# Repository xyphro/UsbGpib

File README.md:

# Table of contents

:newspaper: [Latest updates](Updates.md)
<br> :hammer: [Buy it or build it](#buy-it-or-build-it)
<br> :wave: [UsbGpib Introduction](#usbgpib-introduction)
<br> :house: [Housing / Enclosure](#housings)
<br> :computer: [Software](#software)
<br> &nbsp; &nbsp; :electric_plug: [Using the device](#using-the-device)
<br> &nbsp; &nbsp; :gear: [Setting and getting parameters](#setting-parameters)
<br> :heavy_check_mark: [Testing status](#testing-status)
<br> :notebook: [Tutorials](Tutorials/README.md) <- **New!**
<br> :heart: [Support the Project](#support-the-project)

# Summarized latest updates

For detailed visibility look under the Latest update link above!

[18th Apr 2026]: **Released Firmware V2.4: Added support for multiple GPIB devices**

[18th Apr 2026]: **Added some updated notes on GPIBee**

[07th Mar 2026]: **USbGpib V2 back in Stock on Elecrow**  

[07th Mar 2026]: **10 UsbGpib V3 == GPIBee prototypes ready for testing**

# Next version update USBGpib V3 

**UsbGpib V3 has a Name - Introducing GPIBee**

...and as you’ll see in the picture: The beauties are ready!

After months of development, redesigns, loosing hair on fixing SW bugs and teasing the new Ethernet + PoE capabilities, the next generation of UsbGpib finally has its official identity. From this point forward, UsbGpib V3 will be known as GPIBee - a compact, fast, and delightfully capable little worker that's ready to buzz around your lab equipment.

PoE is fully operational, VXI-11 supports multiple simultaneous connections, and USB High-Speed is performing flawlessly - on MY bench. Which does not mean (yet) on everybody elses bench. Testing is by multiple people is always very important!

I now have ten GPIBee prototypes fully assembled and sitting proudly on my desk. These units will soon head out to the first wave of beta testers who’ve been following the journey and are eager to put them through real‑world use.
I had hoped to start shipping next week, but with Embedded World taking up my entire schedule, distribution will begin shortly after I'm back. The excitement doesn't slow down - it just builds a little more.

Thank you all for the incredible support, feedback, and enthusiasm.

GPIBee is about to take its first flight, and you're part of the swarm that made it possible.
Stay tuned - beta testing starts soon, and the prototypes look fantastic.

## GPIBee update 18th April: 

The first prototypes have been shipped, and internal testing is already well advanced.  
Across all protocols, read performance shows a **3.5× to 5× speed increase**, and this is **without** any dedicated speed-optimization work applied yet.

## Communication Modes

### USB Interface

GPIBee supports three independent USB-based communication modes:

1. **Network mode**  
   GPIBee exposes a USB-based Ethernet interface. An IP address is assigned automatically, enabling true plug-and-play operation.  
   - Full **VXI-11** support  
   - Integrated **web server** providing configuration pages, a GPIB command console, and the complete manual matching the currently installed firmware  
   - Ideal for multi-device setups and remote control - it should be considered as the first Goto solution in terms of USB based modes.

2. **USBTMC mode**  
   Similar to **UsbGpib V2**, but extended with additional commands, including the ability to set the target **GPIB device address** — enabling communication with multiple GPIB instruments.

3. **++ protocol mode**  
   Exposes a **USB CDC UART** implementing the popular ++ protocol, compatible with existing controllers using that protocol — but at significantly higher speed.

The USB modes are **mutually exclusive**. The active mode can be selected via the **web interface** or through internal **SCPI commands**.

### Ethernet Interface

1. **VXI-11**  
   Provides multiple logical channels, allowing communication with several GPIB devices simultaneously without manually switching addresses between commands. 
   - Proper **lock handling** for multi-client access  
   - Full **SRQ** support  
   - Full **GPIB subaddressing** support

2. **++ protocol**  
   Optional **TCP/IP** service on port **1234**, offering the same `++` protocol implementation as in USB CDC UART mode.

Both Ethernet protocols can be **active at the same time**. The Ethernet interface also exposes the same **web interface** as USB network mode, enabling GPIB transfers, configuration changes, and access to the **firmware-synchronized manual**.

## GPIBee Beta Testing Status

The current beta focus remains on **functional correctness and stability**.  
**Speed optimization** will follow next.

For testers not having received an adapter yet: Additional prototype units will be shipped soon. Handling too many testers at once would otherwise become too **time-intensive**.

---

# Buy it or build it

* Tired of tinkering? Want to skip the hassle and get straight to using your GPIB setup?  
* You’d rather spend your time using your instruments instead of assembling hardware?

Skip the soldering iron and jump straight into your GPIB workflow!

You’ve got two solid options to get a ready‑to‑run UsbGpib adapter.

## &#x1f1fa;&#x1f1f8; - United States
* If you're in the US, you can now order the UsbGpibV2 directly from several sources, including my distribution partner Binho LLC. Enjoy fast domestic shipping with no long waits, no customs paperwork, and no surprises - just quick delivery and a smooth experience: 
<br> &#x1F449; <a href="https://binho.io/test-measurement/products/usbgpib-v2/" target="_blank">https://binho.io/test-measurement/products/usbgpib-v2/</a>
<br> &#x1F449; <a href="https://www.digikey.com/short/29nqq5cz" target="_blank"> https://www.digikey.com/short/29nqq5cz</a>
<br> &#x1F449; Amazon US also has it listed, but right now no stock, but worthwhile to check it out there too.

## &#x1F30E; - Worldwide
* I’ve teamed up with Elecrow to bring you ready-to-roll GPIB-USB converters – perfect for those who want results, not a weekend project.
* These adapters come fully assembled, programmed, housed, tested, and ready to go. No fuss. No build. Just plug it in and start working.
* The Adapters match 100% the V2 version described in this repository. 
* &#x1F449; <a href="https://www.elecrow.com/xyphrolabs-gpibusb.html" target="_blank">https://www.elecrow.com/xyphrolabs-gpibusb.html</a>

Let the data flow begin!

This doesn’t mean I’m going fully commercial - far from it.
Offering pre-built adapters is simply a convenience for those who’d rather skip the build and get straight to using their gear.

All sharing, support, and collaboration will remain fully open, just as before.
This is about choice, not change!

The full design files are located in this repository in case you want to build the devices yourself.

---

# UsbGpib Introduction
Versatile, cheap, portable and robust USB to GPIB converter (USBTMC class based).

You'll find many projects like this, but this one is special (ok, everybody will claim this) :-)

V1 Hardware: 

V2 Hardware: 

If you have a lot of test equipment at home, you might know the issues: Lots of devices only have GPIB as interface and the GPIB adapters and GPIB cables on the market are very expensive and some of them even have many issues, when run under Windows 10 (device driver does not work). Or they e.g. are not able to be operated with VISA, because they are UART based, need special command sequences, ...

The adapters are also typically very long, such that they extend the overall length of your test equipment by at least 10cm (~4 inches).

Apart of the 2 very big manufacturers, other GPIB adapters, e.g. with Ethernet or also USB interface are not recognized by normal VISA providers or PyVisa, making the measurement control implementation specific for your GPIB adapter.

I've got frustrated and tried to turn it into something positive. Here a video showing the final device in action - click to view:

Some goals of the project were:
- Work based on the standard USBTMC protocol. This allows the GPIB test equipment to look like a normal USB based measurement device and work flawless with e.g. NI VISA, Labview, Matlab or PyVisa.
- Have a small length - otherwise my equipment has the risk of falling from the shelf :-) Also the USB cable should connect 90 degree angled, to make it very short. With V2 HW, the length got further reduced to the size of a GPIB connector.
- It should be cheap but still versatile (you can build a single one of these for only 14 USD!)
- It should support ALL my test equipment, from many different GPIB implementation generations and different GPIB flavors
- The Firmware should be upgradeable over USB
- It should be rock-solid (!) I don't want to end up in a very long measurement being interrupted because of a software issue of my USB GPIB converter.
- It should support additional features like serial poll, remote enabling/disabling
- If there is no GPIB device connected to the USBGpib converter, or the GPIB device is powered down, there should be no USB device visible on the PC.

All those goals are met.

---

# Hardware

## Microcontroller choice

Although I typically would prefer nowadays an ARM Cortex M0/3/4/7 controller, there is an issue with it. Available devices support only max. 3.3V supply voltages, such that there would be a requirement for a level-shifter towards the GPIB Bus.
GPIB is based on 5V (not exactly true, but a first iteration).

This limited the microcontroller choice to e.g. AVR or PIC controllers. Because of very good availability I ended up in ATMEGA32U4 controllers.
Apart of the device supporting 5V I/O voltages, it also does not require a regulator to be part of the application - it has an internal 3.3V regulator. This minimizes the full application schematic and BOM.

Apart from that, there is an excellent USB stack available [http://www.fourwalledcubicle.com/LUFA.php](http://www.fourwalledcubicle.com/LUFA.php).

The GPIB side of the schematic can be directly connected to the ATMega32U4 IO pins. The IO pins from the microcontroller side are only set to 2 different states: Tri-state (input) or output LOW, to talk over GPIB.

## Component sourcing

All components are easy to source, so I only specify the potential critical ones:

- 16 MHz Crystal: Farnell 2853867 - MCSJK-7E-16.00-8-30-100-B-30 
- REV 1 GPIB connector: Farnell 2421095 - NORCOMP 112-024-113R001. For REV 2 use a straight 24P male solder type connector e.g. from AliExpress.
- USB connector for V1 HW: Farnell 2668483 - Amphenol ICC 61729-1011BLF
- USB connector for V2 HW: Best is to look on AliExpress for 57 series 24P connector as a starting point.

## PCB

The PCB can be ordered at nearly any PCB pool production service (e.g. 10 PCBs for 2 USD + shipping). The gerber files are included in the "HW/Gerber files" subdirectory.

## Mounting the PCB & Flashing the firmware

The PCB is available in 2 revisions.
- [REV 1](HW/REV1/README.md) is the most popularly used right now due to age. It has a USB Type-B connector and an L-shaped housing visible on a few photos of this page.
- [REV 2](HW/REV2/README.md) has some improvements like being smaller, better fit and USB Type-C connector.
- A REV 3 is upcoming. It will be a major redesign with more speed, Ethernet and power over Ethernet support, but the same DNA: Standard protocols being used and ensure compatibility and stability!

Choose whatever you prefer. The software images, but also the external behavior is the same.

---

# Housings

## REV 1

I created a sophisticated 3D printable housing for this adapter. The design was made with Fusion 360. The project file + the STL files are included in the "Housing" sub directory.

The PCB fits perfectly into it. Optionally it can be fixed with 2 mounting screws (the GPIB connector has 2 threads, use 2 times 4-40 UNC x 3/8) and the TOP cover snaps onto the housing base.

I printed this using an Ender 5 3D printer with black PLA, 0.15mm layer height, 1mm wall thickness, no support.
Take care, that you rotate the TOP part of the housing by 180 degrees, so that the flat side is located on the printer bed.
Printing works fine, several iterations of the design were made to ensure good printability.
I printed so far 15 housings, without a single fail.

More information on this REV 1 can be found here: [REV 1](HW/REV1/README.md).
Note, that also the programming/build instructions moved to this location.

## REV 2

The REV 2 housing is a lot smaller, but requires 2 screws.
The housing is quite important to be able to connect and disconnect the board without breaking anything. It is key for mechanical stability of the adapter.
When operating the device without housing, take very well care when plugging in and out the board in case the GPIB connector has a very tight fit.

Information on how to build it can be found in the HW/REV 2 folder: [REV 2](HW/REV2/README.md).
Note, that also the programming/build instructions moved to this location.

---

# Software

## Source code

The source code of the Boot loader (slightly modified LUFA MassStorage Boot loader) and the main USBGPIB converter are located in the "SW" subdirectory.
At the time of publication LUFA 170418 release was used, with GCC as compiler.

Note: The Software is compatible with any HW revision in this repository. For REV 1 and REV 2 hardware you don't need different SW images.

## Binaries

For those, that just want to create their own device, I've included the binary output in the "SW/binaries" subdirectory.

---

# Using the device

## USB enumeration

You might be surprised initially, that the device does not show up in your device manager (or lsusb), when you connect only the USB side. This is a feature, not a bug (really!).
Only, if a GPIB device is connected, you can see the device on your PC too.

The reason behind the feature is simple: Instead of having a standard GPIB wiring, where you have a single GPIB controller and lots of GPIB devices interconnected, USBGPIB supports only a direct connection of the USBGPIB device to your measurement device. If you have like me e.g. 14 Instruments you don't want all to show up in the device manager, if the measurement device itself is powered down - you won't anyway be able to communicate with a powered down device.

When USB and the GPIB side is connected, the device enumerates. The USBGPIB device reads out the ID of the instrument and constructs a unique USB Serial number out of it. It is thus easily possible to assiate multiple connected USBGPIB devices with the measurement instrument.

The VISA ressource name is constructed from this USB Serial number. You can identify easily e.g. in NiMax, which device is connected:

If you connect your USBGPIB device afterwards to another GPIB measurement device, it will disconnect and connect with a new serial number string, matching the other GPIB device *IDN? response again.

## GPIB settings on your measurement device

GPIBUSB does probe all GPIB primary addresses (and secondary address 0) for presence of a GPIB Talker/listener. It is thus not required to set a specific GPIB address - GPIBUSB will find it itself.

The only importance setting on the measurement device is, that the GPIB interface is enabled, which is typically the case.

## LED indicator

The LED indicates different states:

LED blinking: The USBGPIB converter is connected to a measurement instrument, it is powered off or its GPIB port is disabled. In this state, the device is also not connected to USB and will not show up in the device manager or lsusb.
LED on: The device is connected to a measurement device and GPIB communication possible. It is also accessible over USB
LED off: The device is not connected over USB, or the PC powered off :-)

## Controlling GPIB devices

As this converter implements the standard USBTMC Test and measurement class, you can control your instrument from ANY of the normal VISA tools. I tried so far R&S VISA and NI Visa, using Python and Matlab to talk to the devices.

# Testing status

This project is actively maintained since more than 6 years and I personally consider it as very stable. It is proven by multiple users to operate on MacOSX, Linux and Windows and measurement equipment from several decades.

In general I take bug reports very serious and want to "fix them all". In case you don't get an answer on-time on items you report in the issues section, please write me: Xyphro@gmail.com. 
I often miss seeing issue reports very quickly, as I don't get an email once they are filed.

## Sucessfully tested measurement equipment:

Below list is equipment I mainly myself tested. Many other users have other measurement equipment proven in use already.

- R&S FSEM30
- R&S SMIQ03
- R&S CMU200
- R&S SMW200A
- R&S FSW
- R&S FSV
- Keithley 199 multimeter
- HP 34401 DMM from different generations / with different FW versions
- HP 3325A synthesizer/frequency generator
- HP 3457A multimeter
- Agilent E4406A VSA transmitter tester
- Tektronix TDS7104 Digital Phosphor Oscilloscope
- HP 8596A spectrum analyzer
- Agilent E3648A dual power supply

## Scenarious

- It works under all popular operating systems like Windows 7 and 10, 11, Linux and MacOSX
- USB1.1, USB2.0 and USB3.x ports tested, with and without USB HUB in between.
- The connection stays responsive, when power cycling the PC, or hibernating/sleeping it
- Different connection cycles (GPIB side connected first, USB side connected first, swapping GPIB side equipment, ...)
- Extensive testing of timeout scenarious. E.g. making an illegal query and testing, if the USBTMC handles the timeouts properly. This was a very tricky part to get right.
- Tested special transfer modes. E.g. capturing screenshots from different equipment is usually something, which will drive other GPIB adapters to the limits, because binary data of unknown length needs to be transported successfully.

# Setting Parameters

The firmware version from 13th January 2024 onwards has the ability for human readable text base configuration of several parameters.
The previous methods are still supported, but won't be further documented. You can look them back in the history of this file.

The command parser is quite simple. For that reason follow the exact syntax as shown below. 
Don't add extra spaces or make other modifications or concatenate commands.

## Read termination method

While most GPIB interfaces use the hardware signal EOI to signal the end of a message, not all old equipment supports it. Some older instruments even don't have the EOI pin hardware wise wired and use \r or \n termination.

The USB-TMC standard allows to set the read termination. While in firmware versions before < 2.0 I did not enable that method, it is now finally supported with standard compliance.

I document here the older method (using pulse indicator request), but I add also the newer methods which are 100% UsbTmc compliant and portable across different equipments. You can choose which ones to use, but in some cases pulse indicator requests can be difficult to issue, for which reason it is likely better to use the standard compliant method.

### Set read termination to CR (\r):
(old method)
```
dev.control_in(0xa1, 0x40, 0, 0, 1); # USBTMC pulse indicator request (enables internal command processing)
dev.write('!term cr')
```
Above setting is volatile. To make this a permanent setting call the below mentioned "!term store" command.

(prefered method) Alternatively you can set the termination directly with visa means, e.g. using PyVisa:
```
dev.set_visa_attribute(visa.constants.VI_ATTR_TERMCHAR_EN, True)
dev.set_visa_attribute(visa.constants.VI_ATTR_TERMCHAR, ord('\r') )
```

### Set read termination to LF (\n):
(old method)
```
dev.control_in(0xa1, 0x40, 0, 0, 1); # USBTMC pulse indicator request (enables internal command processing)
dev.write('!term lf')
```
Above setting is volatile. To make this a permanent setting call the below mentioned "!term store" command.

(prefered method) Alternatively you can set the termination directly with visa means, e.g. using PyVisa:
```
dev.set_visa_attribute(visa.constants.VI_ATTR_TERMCHAR_EN, True)
dev.set_visa_attribute(visa.constants.VI_ATTR_TERMCHAR, ord('\n') )
```

### Set read termination to EOI only (default setting):
(old method) 
```
dev.control_in(0xa1, 0x40, 0, 0, 1); # USBTMC pulse indicator request (enables internal command processing)
dev.write('!term eoi')
```
Above setting is volatile. To make this a permanent setting call the below mentioned "!term store" command.

(prefered method) Alternatively you can set the termination directly with visa means, e.g. using PyVisa:
```
dev.set_visa_attribute(visa.constants.VI_ATTR_TERMCHAR_EN, False)
dev.set_visa_attribute(visa.constants.VI_ATTR_TERMCHAR, ord('\0') )
```

### Save readtermination setting in eeprom (make them non-volatile)
```
dev.control_in(0xa1, 0x40, 0, 0, 1); # USBTMC pulse indicator request (enables internal command processing)
dev.write('!term store')
```

Above relates to the "old non prefered method". In general it is a good idea to set the read termination volatile and use the above suggested methods highlighted with (prefered method).

### Query current termination setting from device
```
dev.control_in(0xa1, 0x40, 0, 0, 1); # USBTMC pulse indicator request (enables internal command processing)
print(dev.query('!term?'))
```
This returns a text string containing "lf", "cr" or "eoi"

## Multi-device support - Setting the GPIB device target address

Since Firmware version V2.4 USBGpib allows supporting multiple instruments.

While the USBTMC protocol allows only setting a single device to be addressed and composite USB devices are not well supported by all VISA implementations, I decided to add a command to set the address of the GPIB device which is addressed.

There is a minor limitation of this approach, which is that service request SRQ handling is only done properly to the currently selected GPIB device.
Another one is, that users shall never forget to set the GPIB address to the correct setting before issuing a command.

### Setting a primary address only

Substitute the text <Primary_address> with a number from 1 to 30 to set the primary address of the new GPIB device to talk to in following GPIB transactions

```
dev.control_in(0xa1, 0x40, 0, 0, 1);
dev.write('!addr <Primary_address>')
```

### Setting a primary + secondary address

Substitute the text <Primary_address> with a number from 1 to 30 to set the primary address and <Secondary_address> with a number from 0..6 or 96..102 of the new GPIB device to talk to in following GPIB transactions.
Note, that not the full subaddress range of 0..31 or 96..127 is supported as of now - this requires a bit more work. Most common device with subaddresses like R&S CMU200 only are well covered with that current range.

```
dev.control_in(0xa1, 0x40, 0, 0, 1);
dev.write('!addr <Primary_address> <Secondary_address>')
```
### Python wrapper example code for GPIB address setting

```
import pyvisa as visa
dev = 'USB0::0x03EB::0x2065::GPIB_22_14236333938351C00011::INSTR'
rm = visa.ResourceManager()
dev = rm.open_resource(dev, open_timeout=1000)

def set_gpib_addr(primary_address, secondary_address = None):
    dev.control_in(0xa1, 0x40, 0, 0, 1);
    if secondary_address is None:
        dev.write('!addr %d' % primary_address);
    else:
        dev.write('!addr %d %d' % (primary_address, secondary_address));
    
# Address CMU200, which is for me on primary address 1, secondary address 0
set_gpib_addr(1, 0)
print(dev.query('*IDN?'))

# address HP3457A on primary GPIB address 22
set_gpib_addr(22)
dev.write('END,ALWAYS')
print(dev.query('ID?'))
```

This code results in my current testsetup with CMU200 and HP3457A in this output:

```
Rohde&Schwarz,CMU 200-1100.0008.02,xxxxxx,V5.22

HP3457A
```

## AutoID setting

Default wise the GPIB adapter tries during power on of the instrument to query using *IDN? or ID? commands the instrument name automatically.
This is used to build the USB serial number, which finally gets part of the VISA ressource string.

Not all instruments support this *IDN / ID? query. For this reason this feature can be turned off.
The serial number will then be built based on the GPIB address of the instrument.

### Turn AutoID feature off
```
dev.control_in(0xa1, 0x40, 0, 0, 1); # USBTMC pulse indicator request (enables internal command processing)
dev.write('!autoid off')
```
This setting is stored in eeprom = non volatile memory, so will survive a power cycle

### Turn AutoID feature on
```
dev.control_in(0xa1, 0x40, 0, 0, 1); # USBTMC pulse indicator request (enables internal command processing)
dev.write('!autoid on')
```
This setting is stored in eeprom = non volatile memory, so will survive a power cycle

### turn auto ID on with delay

Some instruments need after turn on some seconds before GPIB is responsive.

With below 3 settings you can set a delay which is applied before the instrument ID is queried after power on.
Note that it will take then also more time, before the USB device is recognized by the PC.

Also this setting is non-volatile.

Delay 5 seconds:
```
dev.control_in(0xa1, 0x40, 0, 0, 1); # USBTMC pulse indicator request (enables internal command processing)
dev.write('!autoid slow')
```

Delay 15 seconds:
```
dev.control_in(0xa1, 0x40, 0, 0, 1); # USBTMC pulse indicator request (enables internal command processing)
dev.write('!autoid slower')
```

Delay 30 seconds:
```
dev.control_in(0xa1, 0x40, 0, 0, 1); # USBTMC pulse indicator request (enables internal command processing)
dev.write('!autoid slowest')
```

### read autoid setting

```
dev.control_in(0xa1, 0x40, 0, 0, 1); # 
print(dev.query('!autoid?'))
```
Returns as text string either: "off", "on", "slow", "slower" or "slowest".

## Firmware version

Finally I implemented a command to query the USB adapters firmware version :-)

```
dev.control_in(0xa1, 0x40, 0, 0, 1); # USBTMC pulse indicator request (enables internal command processing)
print(dev.query('!ver?'))
```

## Shorten ressource strings (Matlab)

A user discovered that Matlab has a limitation in the VISA ressource string length and shared a pull request to reduce the length.
I expose this now first time in the baseline firmware with the following options.

This setting is stored in eeprom = non volatile.

### Limit the USB serial number to a length of 20 characters
```
dev.control_in(0xa1, 0x40, 0, 0, 1); # USBTMC pulse indicator request (enables internal command processing)
dev.write('!string short')
```

### disable limitation of USB serial number length (default behavior)
```
dev.control_in(0xa1, 0x40, 0, 0, 1); # USBTMC pulse indicator request (enables internal command processing)
dev.write('!string normal')
```

### query the string length setting.
```
dev.control_in(0xa1, 0x40, 0, 0, 1); # USBTMC pulse indicator request (enables internal command processing)
print(dev.query('!string?'))
```

This returns as text string either "normal" or "short".

## reset the adapter
```
dev.control_in(0xa1, 0x40, 0, 0, 1); 
dev.write('!reset')
```

Do a reset of the adapter. Note that due to the reset you have to close the visa session and start a new one as the device re-enumerates on the USB.

---

# Support the project

Or support by buying a fully prebuilt adapter at: <a href="https://www.elecrow.com/xyphrolabs-gpibusb.html" target="_blank">https://www.elecrow.com/xyphrolabs-gpibusb.html</a>

In general any email, post or feedback is also very valuable, and don't feel bad if you don't use the support options :-)
Feel free to contact me at Xyphro@gmail.com

---

This page is from XyphroLabs UsbGpib project: <a href="https://github.com/xyphro/UsbGpib" target="_blank">https://github.com/xyphro/UsbGpib</a>

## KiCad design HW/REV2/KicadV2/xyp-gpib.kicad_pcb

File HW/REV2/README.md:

# xyphro UsbGpib HW REV 2

The new HW revision picks up some things that I and other misliked:
- The REV 1 HW - when put beeing assembled into its housing did have change to colide with parts of the instruments body. Especially for Keysight equipment. This new HW revision follows the formfactor of an original GPIB cable to get rid of this mechanical constraint.
- The REV 1 HW required to enter the bootloader with a tweezer. REV 2 has a button. Hold it a few seconds and the bootloader is entered.

The [software](../../SW) will always stay the same, no matter if REV1 or REV 2.

I have built many of those adapters myself so far and have developed trust in the design:

## PCB Production

The PCB is designed for the 4-layer JLC04161H-3313 stackup from JLCPCB (impedance matching for USB 90Ohm). However, most FR4-based stackups with ~0.1mm Prepreg (e.g. material between top layer and inner layer 1) should be fine. Additional informations:
- Outer copper 1oz, inner 0.5oz
- Hole size 0.3mm (inner diameter), 0.45mm (outer diameter)
- 5mil trace width and spacing

## Assembly process

All files related to HW are located in this folder. Gerber file, BOM, Kicad design files.

## preparing the PCB

Mount only the SMD components. This means: DON'T mount the GPIB connector yet.

On edge you can find a mounting point for a pinheader - 45 degrees angled. Mount 2-3 pin pinheaders here and you now have a 6 pin ISP programming port with standard pinout for your favorit AVR programmer.
Program the bootloader. Pin 1 is marked on the PCB to allow you connecting the ISP cable in the correct orientation.

### Flashing the Microcontroller first time

For initial programming an AVR ISP adapter is needed to program the "Bootloader.hex" file.

It is very important, that the Fuses of the AVR are programmed.

Here an example how to program the bootloader using avrdude (using usbasp programmer):
avrdude -c usbasp -p m32u4 -e -Ulock:w:0xFF:m -Uefuse:w:0xcb:m -Uhfuse:w:0xd8:m -Ulfuse:w:0xde:m

avrdude -c usbasp -p m32u4 -U flash:w:BootLoader.hex

To program bootloader and application image at the same time using AvrDude, you can use this command:
..\avrdude -c usbasp -p m32u4 -e -Ulock:w:0x3F:m -Uefuse:w:0xcb:m -Uhfuse:w:0xd8:m -Ulfuse:w:0xde:m -U flash:w:TestAndMeasurement.hex -U flash:w:BootLoader.hex

Note, that some programmers use a quite high clock frequency on the programming interface. In case of failures try to decrease the SCK clock frequency!

After programming the file, disconnect and connect the device and a USB drive will show up. Copy the TestAndMeasurement.bin file to this USB drive - ideally using the command line. Example: `copy TestAndMeasurement.bin F:\FLASH.BIN`.
On Linux, there is a bug with the LUFA mass storage that means it is required to use `dd if=TestAndMeasurement.bin of=/mnt/FLASH.BIN bs=512 conv=notrunc oflag=direct,sync`.

When done, disconnect USB.

It is now safe to desolder the ISP pinheaders such that the PCB fits into the housing. 
Any further update can happen over USB using the bootloader.

## Building the whole thing together
Preparation:
- Mount the PCB EXCLUDING the GPIB connector.
- Print the housings located in [this folder](../../Housing/Rev2). I print them using 1mm bottom/top/wall thickness, 0.16mm layer height and 30% infil. On my K1 printer it takes 23 minutes to print, on my Ender 5 2.2 hours.
- get 2 20mm M3 screws and 2 M3 nuts
- get a GPIB connector "24P Male solder type" from e.g. Aliexpress

If you have everything in place and prepared, insert the PCB including the GPIB connector (unsoldered!) into the bigger part of the housing:

Then solder 2 pins of the GPIB connector and take the PCB out of the housing again to solder all pins.
(This step is required to ensure that the GPIB connector has the right distance to the PCB and fit into the housing)

As a next step insert the PCB into the big part of the housing again. It has a relatively tight fit - to ensure mechanic stability.

Then put the smaller part of the housing on top of it, insert the screws (they can be pushed hard to destroy the "membrane" first time) and nuts and screw it together.

Voilà.. your adapter is finished and ready to use :-)

# Updating the firmware at later stages

To enter the boot loader at later stages for updates, press the button (bigger hole in the housing) using a pen/paperclip for about 3 seconds. Then a USB mass storage (flash drive) enumerates on the PC where the firmware image can be copied too (see previous chapter).

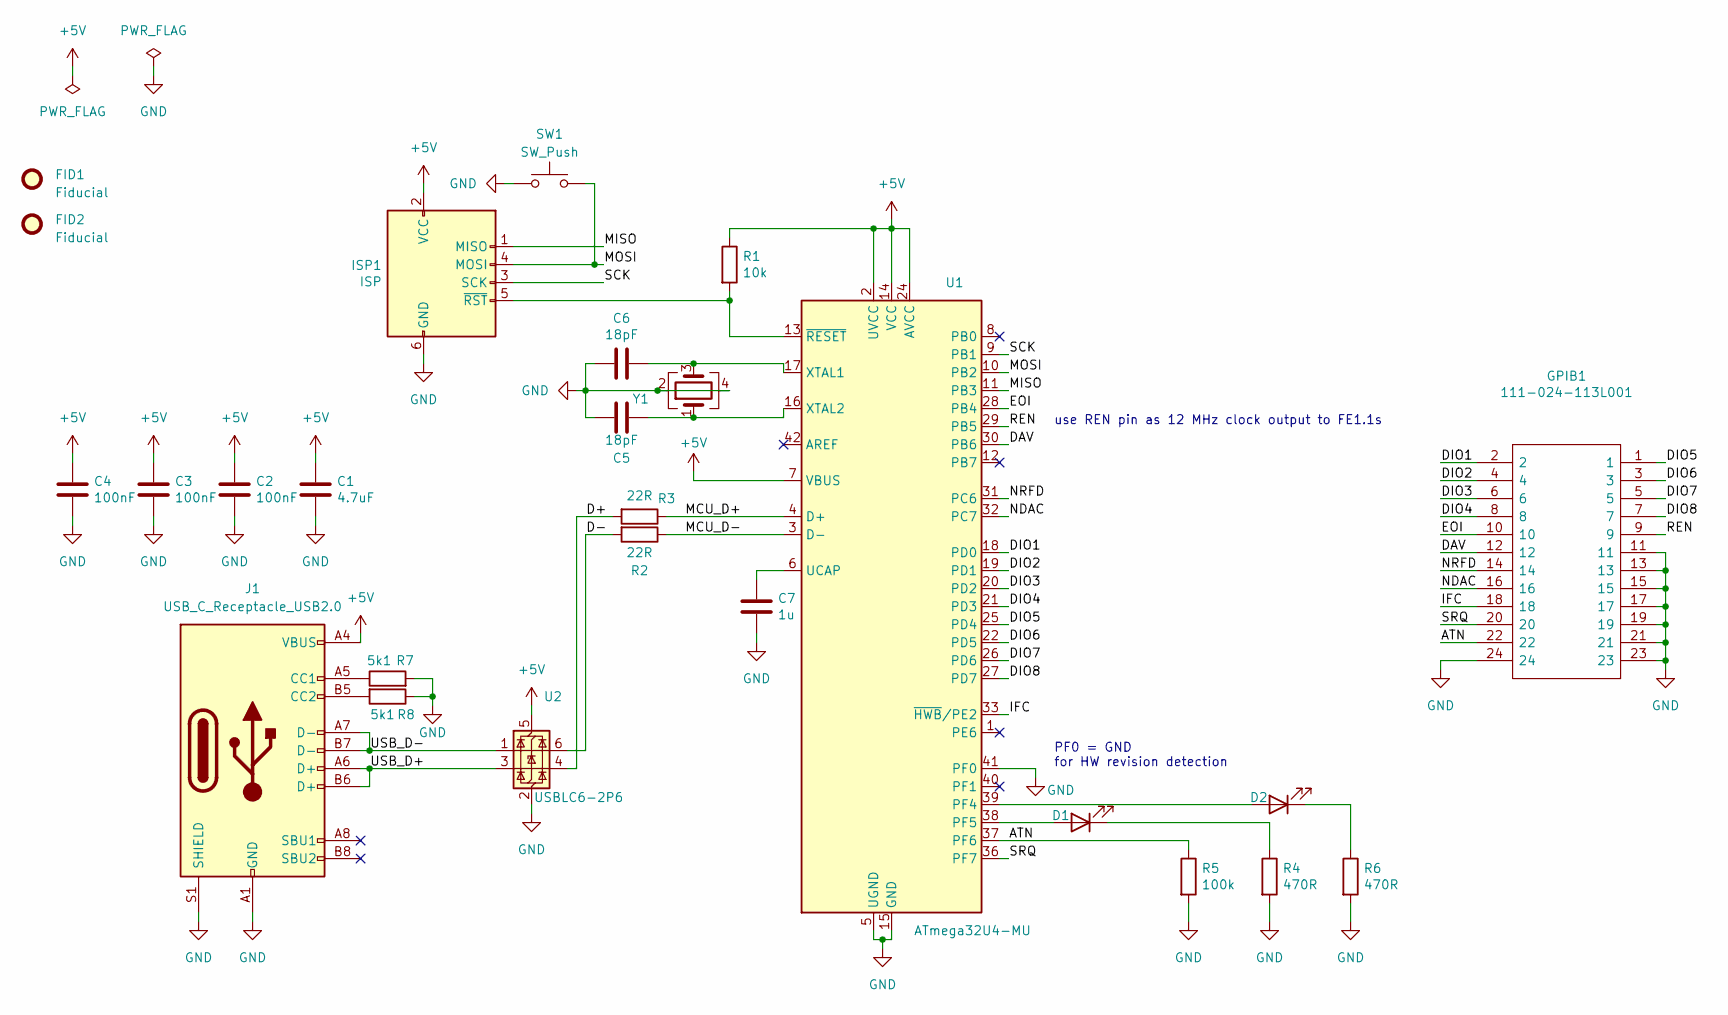
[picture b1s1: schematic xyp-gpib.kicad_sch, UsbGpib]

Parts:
C1: 4.7uF; C_0805_2012Metric
C2, C3, C4: 100nF; C_0603_1608Metric
C5, C6: 18pF; C_0603_1608Metric
C7: 1u; C_0603_1608Metric
D1, D2: LED; LED_0805_2012Metric
FID1, FID2: Fiducial; Fiducial_0.5mm_Mask1mm
GPIB1: 111-024-113L001; GPIB; Manufacturer_Part_Number 112-024-113R001; Mouser Part Number 636-112-024-113R001
ISP1: ISP; EdgeProg-ISP
J1: USB_C_Receptacle_USB2.0; USB_C_Receptacle_XKB_U262-16XN-4BVC11
R1: 10k; R_0603_1608Metric
R2, R3: 22R; R_0603_1608Metric
R4, R6: 470R; R_0603_1608Metric
R5: 100k; R_0603_1608Metric
R7, R8: 5k1; R_0603_1608Metric
SW1: SW_Push; SW_Tactile_SPST_NO_Straight_CK_PTS636Sx25SMTRLFS
U1: ATmega32U4-MU; QFN-44-1EP_7x7mm_P0.5mm_EP5.2x5.2mm
U2: USBLC6-2P6; SOT-666
Y1: CX2016DB16000D0WZRC1; Crystal_SMD_2016-4Pin_2.0x1.6mm

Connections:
+5V: C1.1, C2.1, C3.1, C4.1, ISP1.2 (VCC), J1.A4 (VBUS), J1.A9 (VBUS), J1.B4 (VBUS), J1.B9 (VBUS), R1.1, U1.2 (UVCC), U1.7 (VBUS), U1.14 (VCC), U1.24 (AVCC), U1.34 (VCC), U1.44 (AVCC), U2.5 (VBUS)
/ATN: GPIB1.22, R5.1, U1.37 (PF6)
/D+: R3.2, U2.4 (I/O2)
/D-: R2.2, U2.6 (I/O1)
/DAV: GPIB1.12, U1.30 (PB6)
/DIO1: GPIB1.2, U1.18 (PD0)
/DIO2: GPIB1.4, U1.19 (PD1)
/DIO3: GPIB1.6, U1.20 (PD2)
/DIO4: GPIB1.8, U1.21 (PD3)
/DIO5: GPIB1.1, U1.25 (PD4)
/DIO6: GPIB1.3, U1.22 (PD5)
/DIO7: GPIB1.5, U1.26 (PD6)
/DIO8: GPIB1.7, U1.27 (PD7)
/EOI: GPIB1.10, U1.28 (PB4)
/IFC: GPIB1.18, U1.33 (~HWB/PE2)
/MCU_D+: R3.1, U1.4 (D+)
/MCU_D-: R2.1, U1.3 (D-)
/MISO: ISP1.1 (MISO), U1.11 (PB3)
/MOSI: ISP1.4 (MOSI), SW1.2, U1.10 (PB2)
/NDAC: GPIB1.16, U1.32 (PC7)
/NRFD: GPIB1.14, U1.31 (PC6)
/REN: GPIB1.9, U1.29 (PB5)
/SCK: ISP1.3 (SCK), U1.9 (PB1)
/SRQ: GPIB1.20, U1.36 (PF7)
/USB_D+: J1.A6 (D+), J1.B6 (D+), U2.3 (I/O2)
/USB_D-: J1.A7 (D-), J1.B7 (D-), U2.1 (I/O1)
GND: C1.2, C2.2, C3.2, C4.2, C5.2, C6.2, C7.2, GPIB1.11, GPIB1.13, GPIB1.15, GPIB1.17, GPIB1.19, GPIB1.21, GPIB1.23, GPIB1.24, ISP1.6 (GND), J1.A1 (GND), J1.A12 (GND), J1.B1 (GND), J1.B12 (GND), J1.S1 (SHIELD), R4.2, R5.2, R6.2, R7.2, R8.1, SW1.1, U1.5 (UGND), U1.15 (GND), U1.23 (GND), U1.35 (GND), U1.41 (PF0), U1.43 (GND), U1.45 (GND), U2.2 (GND), Y1.2, Y1.4
unnamed: D1.2 (A), U1.38 (PF5)
unnamed: D1.1 (K), R4.1
unnamed: D2.2 (A), U1.39 (PF4)
unnamed: D2.1 (K), R6.1
unnamed: ISP1.5 (~RST), R1.2, U1.13 (~RESET)
unnamed: J1.A5 (CC1), R7.1
unnamed: J1.B5 (CC2), R8.2
unnamed: C7.1, U1.6 (UCAP)
unnamed: C6.1, U1.17 (XTAL1), Y1.3
unnamed: C5.1, U1.16 (XTAL2), Y1.1

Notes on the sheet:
PF0 = GND for HW revision detection
use REN pin as 12 MHz clock output to FE1.1s

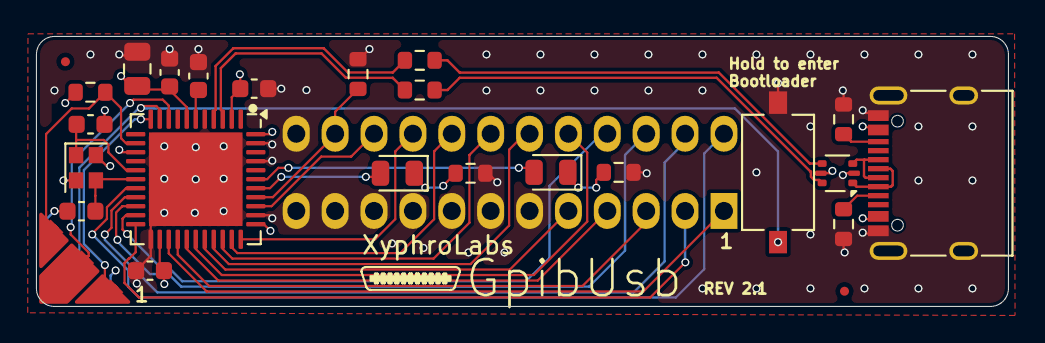
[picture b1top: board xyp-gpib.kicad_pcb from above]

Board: 4 copper layers, 54.0 x 15.0 mm, 26 parts (1 on the bottom side), 37 nets.

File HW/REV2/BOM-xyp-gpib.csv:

Comment,Designator,Footprint,LCSC
ATmega32U4-MU,U1,QFN-44-1EP_7x7mm_P0.5mm_EP5.2x5.2mm,C112161
SW_Push,SW1,SW_Tactile_SPST_NO_Straight_CK_PTS636Sx25SMTRLFS,C118141
100nF,"C2,C3,C4",C_0603_1608Metric,C14663
1u,C7,C_0603_1608Metric,C15849
18pF,"C5,C6",C_0603_1608Metric,C1647
4.7uF,C1,C_0805_2012Metric,C1779
470R,"R4,R6",R_0603_1608Metric,C23179
5k1,"R7,R8",R_0603_1608Metric,C23186
22R,"R2,R3",R_0603_1608Metric,C23345
100k,R5,R_0603_1608Metric,C25803
10k,R1,R_0603_1608Metric,C25804
CX2016DB16000D0WZRC1,Y1,Crystal_SMD_2016-4Pin_2.0x1.6mm,C2682780
USB_C_Receptacle_USB2.0,J1,USB_C_Receptacle_XKB_U262-16XN-4BVC11,C2936185
LED,"D1,D2",LED_0805_2012Metric,C84256
USBLC6-2P6,U2,SOT-666,C15999

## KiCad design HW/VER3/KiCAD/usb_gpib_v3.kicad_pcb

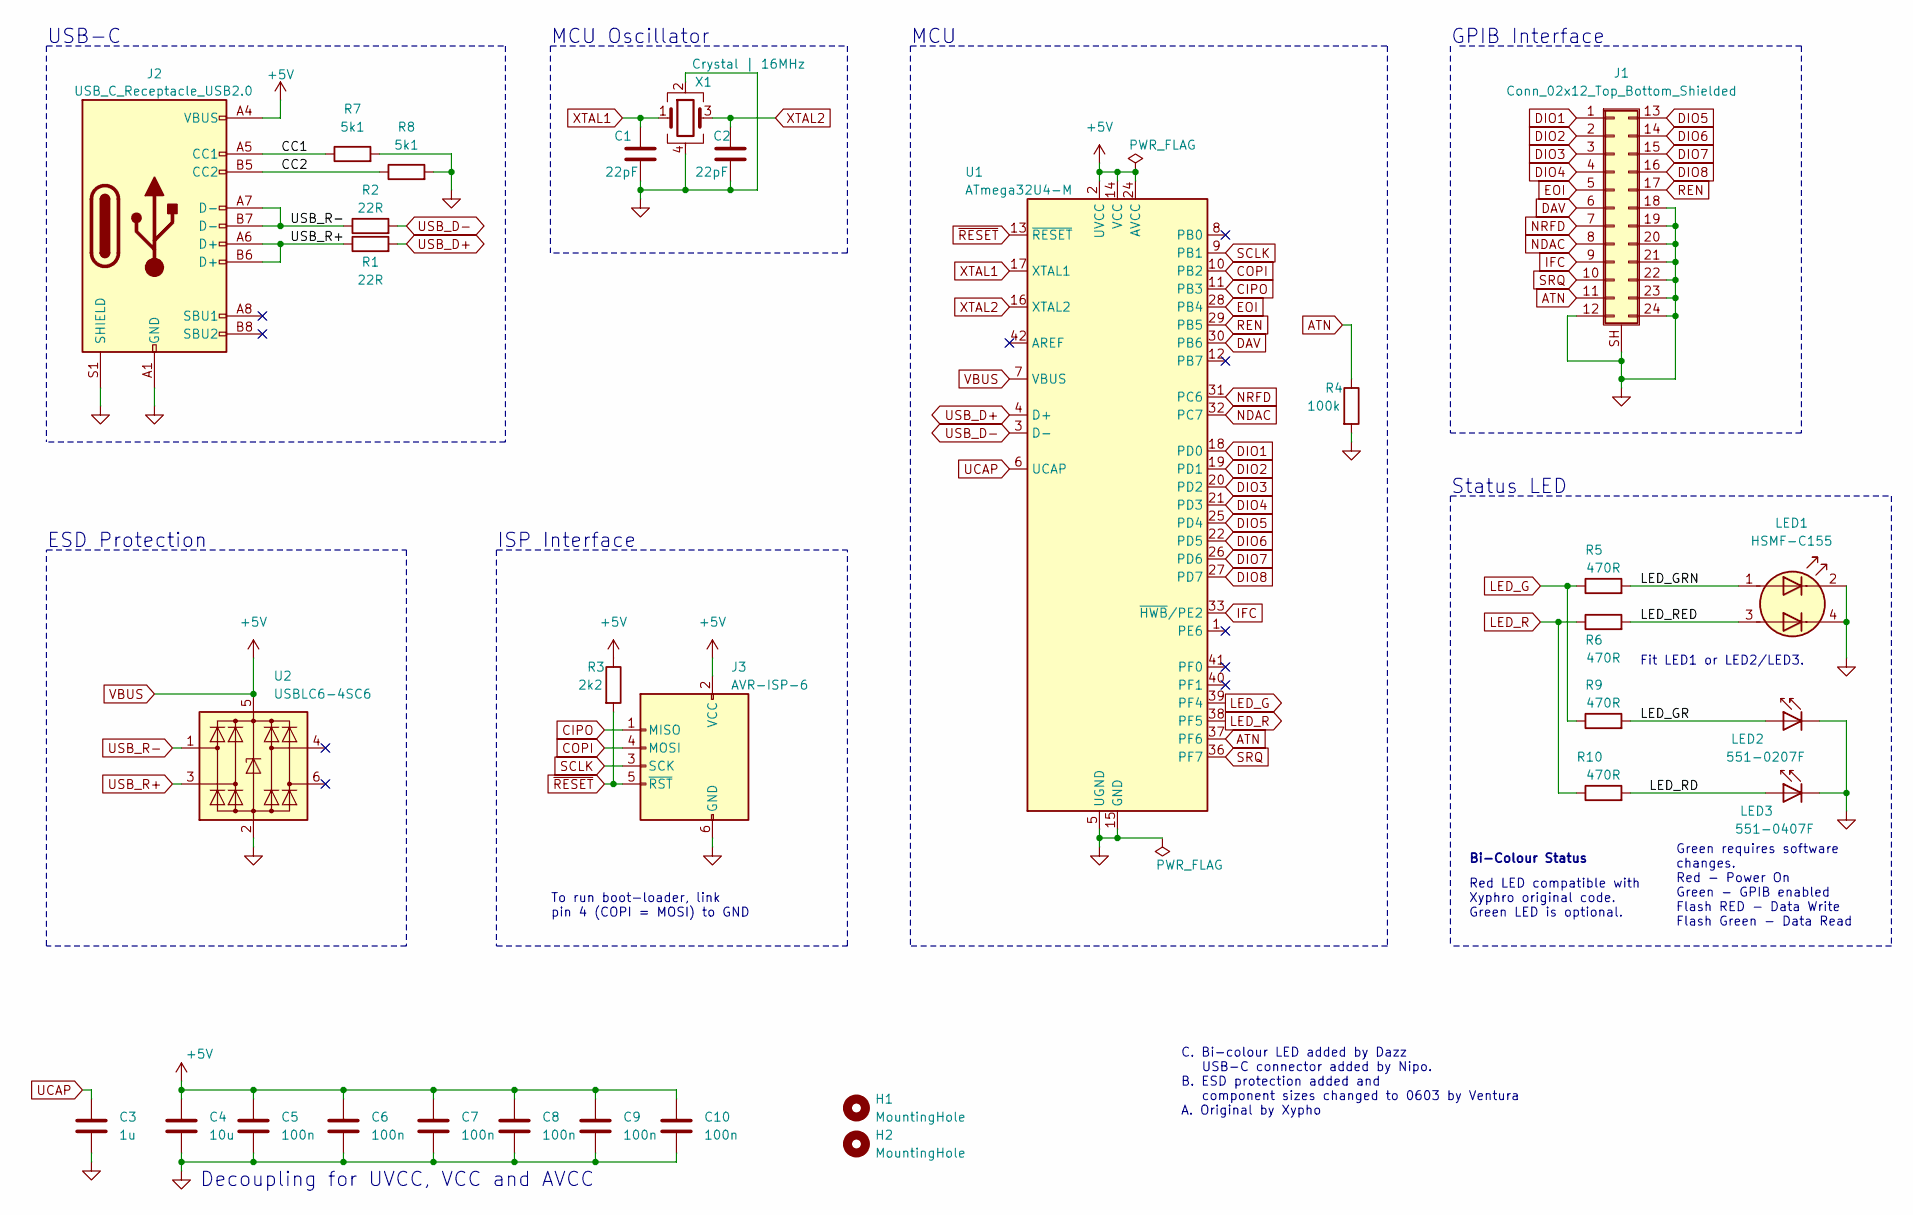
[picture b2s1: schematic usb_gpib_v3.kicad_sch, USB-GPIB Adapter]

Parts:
C1, C2: 22pF; C_0603_1608Metric_Pad1.08x0.95mm_HandSolder
C3: 1u; C_0603_1608Metric_Pad1.08x0.95mm_HandSolder
C4: 10u; C_0603_1608Metric_Pad1.08x0.95mm_HandSolder
C5, C6, C7, C8, C9, C10: 100n; C_0603_1608Metric_Pad1.08x0.95mm_HandSolder
H1, H2: MountingHole; MountingHole_2.7mm_M2.5_DIN965
J1: Conn_02x12_Top_Bottom_Shielded; 112-024-113R001
J2: USB_C_Receptacle_USB2.0; USB_C_Receptacle_HRO_TYPE-C-31-M-12; MPN CX90M-16P; Digi-Key CX90M-16P
J3: AVR-ISP-6; PinHeader_2x03_P2.54mm_Vertical
LED1: HSMF-C155
LED2: 551-0207F; LED_D3.0_Horizontal_Dialight_Z5mm
LED3: 551-0407F; LED_D3.0_Horizontal_Dialight_Z5mm
R1, R2: 22R; R_0603_1608Metric_Pad0.98x0.95mm_HandSolder; LCSC C25905
R3: 2k2; R_0603_1608Metric_Pad0.98x0.95mm_HandSolder
R4: 100k; R_0603_1608Metric_Pad0.98x0.95mm_HandSolder
R5, R6, R9, R10: 470R; R_0603_1608Metric_Pad0.98x0.95mm_HandSolder; LCSC C25117
R7, R8: 5k1; R_0603_1608Metric_Pad0.98x0.95mm_HandSolder; LCSC C25905
U1: ATmega32U4-M; TQFP-44_10x10mm_P0.8mm
U2: USBLC6-4SC6; SOT-23-6
X1: Crystal | 16MHz; Crystal_SMD_3225-4Pin_3.2x2.5mm_HandSoldering

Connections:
/CC1: J2.A5 (CC1), R7.1
/CC2: J2.B5 (CC2), R8.1
/LED_GR: LED2.2 (A), R9.2
/LED_GRN: LED1.1 (A1), R5.2
/LED_RD: LED3.2 (A), R10.2
/LED_RED: LED1.3 (A2), R6.2
ATN: J1.11, R4.1, U1.37 (PF6)
CIPO: J3.1 (MISO), U1.11 (PB3)
COPI: J3.4 (MOSI), U1.10 (PB2)
DAV: J1.6, U1.30 (PB6)
DIO1: J1.1, U1.18 (PD0)
DIO2: J1.2, U1.19 (PD1)
DIO3: J1.3, U1.20 (PD2)
DIO4: J1.4, U1.21 (PD3)
DIO5: J1.13, U1.25 (PD4)
DIO6: J1.14, U1.22 (PD5)
DIO7: J1.15, U1.26 (PD6)
DIO8: J1.16, U1.27 (PD7)
EOI: J1.5, U1.28 (PB4)
GND: C1.1, C2.1, C3.2, C4.2, C5.2, C6.2, C7.2, C8.2, C9.2, C10.2, J1.12, J1.18, J1.19, J1.20, J1.21, J1.22, J1.23, J1.24, J1.SH (Shield), J2.A1 (GND), J2.A12 (GND), J2.B1 (GND), J2.B12 (GND), J2.S1 (SHIELD), J3.6 (GND), LED1.2 (K1), LED1.4 (K2), LED2.1 (K), LED3.1 (K), R4.2, R7.2, R8.2, U1.5 (UGND), U1.15 (GND), U1.23 (GND), U1.35 (GND), U1.43 (GND), U2.2 (GND), X1.2, X1.4
IFC: J1.9, U1.33 (~HWB/PE2)
LED_G: R5.1, R9.1, U1.39 (PF4)
LED_R: R6.1, R10.1, U1.38 (PF5)
NDAC: J1.8, U1.32 (PC7)
NRFD: J1.7, U1.31 (PC6)
REN: J1.17, U1.29 (PB5)
SCLK: J3.3 (SCK), U1.9 (PB1)
SRQ: J1.10, U1.36 (PF7)
UCAP: C3.1, U1.6 (UCAP)
USB_D+: R1.2, U1.4 (D+)
USB_D-: R2.2, U1.3 (D-)
USB_R+: J2.A6 (D+), J2.B6 (D+), R1.1, U2.3 (I/O2)
USB_R-: J2.A7 (D-), J2.B7 (D-), R2.1, U2.1 (I/O1)
VBUS: C4.1, C5.1, C6.1, C7.1, C8.1, C9.1, C10.1, J2.A4 (VBUS), J2.A9 (VBUS), J2.B4 (VBUS), J2.B9 (VBUS), J3.2 (VCC), R3.1, U1.2 (UVCC), U1.7 (VBUS), U1.14 (VCC), U1.24 (AVCC), U1.34 (VCC), U1.44 (AVCC), U2.5 (VBUS)
XTAL1: C1.2, U1.17 (XTAL1), X1.1
XTAL2: C2.2, U1.16 (XTAL2), X1.3
~RESET: J3.5 (~RST), R3.2, U1.13 (~RESET)

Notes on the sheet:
Status LED
ESD Protection
GPIB Interface
ISP Interface
MCU
Green requires software changes. Red - Power On Green - GPIB enabled Flash RED - Data Write Flash Green - Data Read
Red LED compatible with Xyphro original code. Green LED is optional.
MCU Oscillator
C. Bi-colour LED added by Dazz USB-C connector added by Nipo. B. ESD protection added and component sizes changed to 0603 by Ventura A. Original by Xypho
Bi-Colour Status
Decoupling for UVCC, VCC and AVCC
To run boot-loader, link pin 4 (COPI = MOSI) to GND
Fit LED1 or LED2/LED3.
USB-C

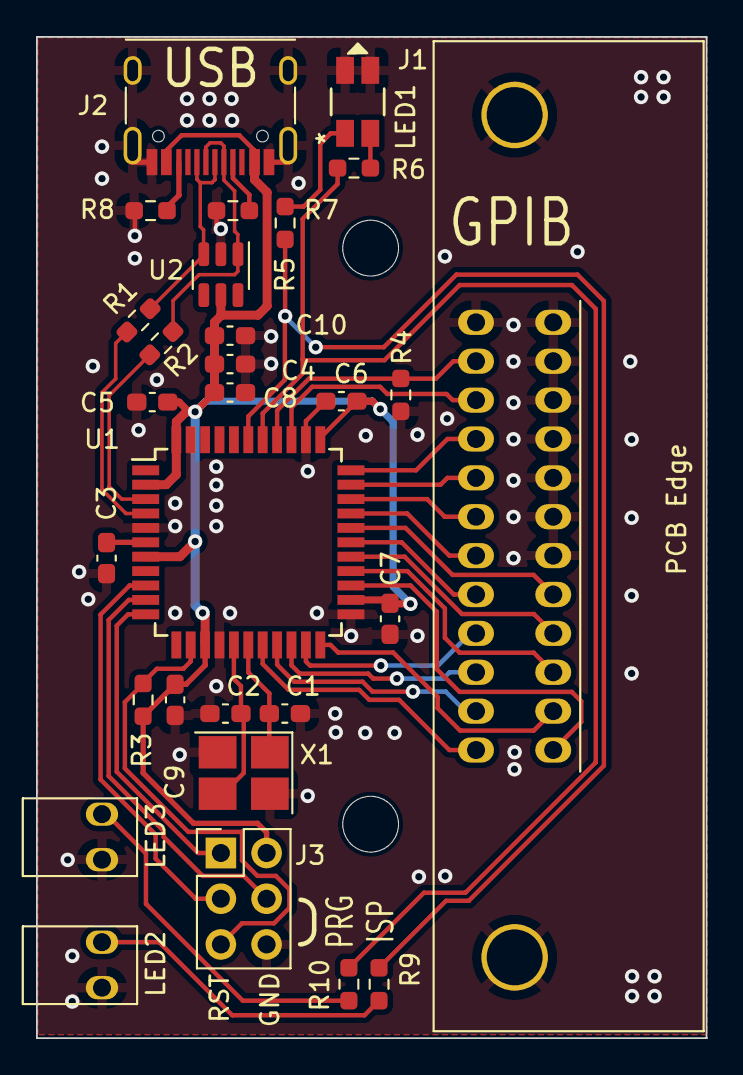
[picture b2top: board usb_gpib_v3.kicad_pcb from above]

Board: 2 copper layers, 37.2 x 55.6 mm, 31 parts (0 on the bottom side), 37 nets.

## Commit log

2019-11-01 Initial full project commit
2019-11-01 Adding PCB of Gerber files
2019-11-01 adding 2 pictures
2019-11-01 adding NiMaxScreenshot with FSEM30 beeing connected
2019-11-01 Create LICENSE
2019-11-01 fixed some typos/extended description
2019-11-02 Adding a youtube video to readme.md
2020-04-23 Added PCB with 0603 components iso. 0402
    Added alternative version of PCB with 0603 components intead of the tiny 0402 (thanks @DaviVolcan!)
2020-04-23 Added avrdude commands (thanks @motechsolutions)
2020-04-26 Added parameters to select read termination + turn off automatic ID readout.
    On top of that a method is implemented to set these instrument specific parameters using a certain sequence of indicator pulse command and command writing.
    Updated readme.md documentation accordingly to reflect those new features (see last section).
2021-05-08 Adding gerber files for big components variant
    Adding Gerber files for PCB variants with 0603 components (biggercomponents)
2021-12-24 files for VQFN version of pcb
2021-12-26 updated to reflect the release of kicad 6.0.
2022-05-03 Add V2 of the design
    This modified HW supports QFN and TQFP IC variants on a single PCB. 0402 components have been changed to 0603 size for easier soldering.
    SW support for AtMega16U4 variant will come soon.
2022-11-23 Document workaround to load FW on Linux host
    Refer #11
2023-06-05 Add additional VISA resource names options
2023-06-05 Correct some typos in README.md
2023-10-17 October 2023 updates
    - 488.2 support is enabled.
    - fixed issue: Linux PCs show that Config 1 descriptor is not correct.
    - Fixed read status byte, Clear and trigger assertion functions.
    - Compatibility with R&S Visa is back - it got broken in a previous version. Read status byte, Clear and trigger did not work properly.
    - I deleted 2 HW variants to avoid confusion. Right now there is one Eagle 6 version (mine) and a user contributed Kicad version included.
2023-10-30 Fix for Issue report #38
    Fix for Issue #38
    https://github.com/xyphro/UsbGpib/issues/38
    On old FW revision HP34401 multimeter issues occured. The multimeter froze in remote mode and could not be put back to local, the read queries stopped after some time.
    As it turned out, this was related to ATN line timing (which is rather unspecified). Inserting defined delays on ATN line status changes like NI GPIB-USB-HS does fixed the issue reportedly. Thanks Ch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
2023-10-30 outlook
    Added outlook for next HW revision and some notes on the current FW status.
2023-10-30 fixed readme.md issue
2023-11-04 Improved the printability of the screw holes
    By putting a "thin solid wall", which acts as support when printing the screw hole. This prevents sagging of filament.
2023-11-07 add revision 2 photo
2023-11-07 Update README.md
    Added revision 2 outlook photo.
2023-11-12 Add picture of upcoming Rev 2
2023-11-12 Update README.md
    Fixed description of control_in for termination setting
2023-11-19 Update Setting Parameters chapter in README.md
    - whole chapter restructured
    -described new VISA resource name options
2023-11-19 Add startup delay, when an instrument is powered on after the USBGPIB
2023-11-19 update README, adding startup delay command info
2023-12-05 Aktualisieren von README.md
2023-12-19 Add REV 2 and ReleaseCandidate FW image
2023-12-19 Fix broken image link
2023-12-19 fix a wrong image link
2023-12-19 image link fixed
2023-12-22 Add BOM and CPL file
2023-12-30 Update README.md
    re-added previously accidentally deleted fix for control_in documentation.
2024-01-06 Update README.md
    Slight update to point to the new HW specific README.md files including programming instructions...
2024-01-13 some fixes and full firmware baselining
    - BOM/CPL file: ensure that both R7, R8 have 5K1 value
    - adjusted fuses for programming instructions
    - added Dazz100 suggestion in programming instructions allowing to program bootloader and application image at the same time using AvrDude
    - included sourcecode of current baseline firmware
    - updated firmware: new human readable internal commands realized
    - updated firmware: Fixed issue where after a device clear a query could fail
2024-01-13 fix stupid typo
    Yes, there are many more, but my editor has no spell checker and I am lazy to be frank...
2024-01-15 Fixing presence detection issue
    Hotfix: Fixing, that the adapter did sometimes not detect that the instrument was powered off. Increased FW version to V1.7
2024-06-04 Add release binary build workflow
2024-08-03 Update to KiCAD 8.0.4 and add Digi-Key part numbers.
2024-08-18 Fix pinout and pin 1 orientation of GPIB connector.
2024-10-25 source code for version 2, ready for release
2024-10-25 Windows batch file to process the firmware.
2024-10-25 Linux script to compile and load the firmware.
2024-10-25 Modified for version 2 software.
2024-10-25 Original. To explain why I aimed to modify and enhance the XyPhro adapter.
2024-10-25 To update the Xyphro README to include the version 2 software modifications and enhancements.
2024-10-26 upgraded to version 2 firmware
2024-10-26 Source code for V2 firmware
2024-10-26 Deleted all version 1 files pulled from Xyphro repository. Added version 2 hardware and software files.
2024-10-26 Clearing out ver 1 files. Adding in ver 2 binaries.
2024-10-26 Adding binary files to git.
2024-10-26 Deleted duplicate pictures in HW.
2024-10-26 rewriting README
2024-10-27 Deleting README.md
2024-10-27 Rewriting as part of clearing out version 1 stuff and updating to ver 2e
2024-10-27 Deleting README2.md
2024-10-27 Adding and deleting photos
2024-10-27 Changing names of images to something meaningful.
2024-10-27 Adding photos.
2024-10-28 Removed leaded MCU. Tidied up spreadsheet.
2024-10-28 added details for I ordered from Aliexpress, but available from element14.
2024-10-28 Explaining intermittent flashing of green LED.
2024-10-28 Corrected typo
2024-10-28 identified element14 part numbers for all components.
2024-10-28 Improved formatting. Added some additional explanations.
2024-11-07 Updated README.md to version 3 enclosure.
2024-11-07 Updating all files to version 3.
2024-11-07 "Updating files to version 3e"
2024-11-08 Updating to version 3 files
2024-11-08 "Adding files to version 3 branch"
2024-11-18 Added photos of usb-gpib adapter in use.
2024-12-01 Changed firmware version to V2e0
2024-12-09 Adding config read/write python script.
2024-12-09 Adding adding usage comments to usbgpib_conf.py script
2024-12-31 Correct typ README.md
2025-01-11 Updated FW Version and release of first UsbGpib GUI version
2025-01-11 typo fix
2025-01-12 gui bugfix
2025-01-26 Minor edits to README files
2025-01-26 More doc edits
2025-01-27 added Jims GUI
2025-02-03 Add Jims nicegui readme.md, confscript, fix some typos, etc.
2025-02-03 fix image links
2025-02-03 fix image width
2025-02-05 Added flashing instructions for AVRDUDE
    Added AVRDUDE and a set of commands that worked for me.
2025-04-06 Release of FW V 1.9
    + fix some formating / typing issues.
2025-04-06 Fix issue in UsbGpibGUI
    When reading autoid slow setting, one comboBox showed an empty entry instead of SLOW.
2025-04-21 Release of FW version 2.0
    Changes:
    - fix autoid slower and autoid slowest options
    - Implement USBTMC compliant method to set read termination method
    - Made pulse indicator request function work asynchronous
    See README.MD for more details.
2025-05-08 [MOD] Cleanup schematic + add USBLC6-2P6
2025-05-08 [ADD] Net class to all USB lines
2025-05-09 [MOD] Re-route with proper rules and USBLC6-2P6
2025-05-09 [ADD] Fabrication output and Rev. 2.1
2025-05-09 [FIX] Value of C5/C6 seems to be wrong
2025-06-24 add the possibility to set any termination character from VISA
2025-09-02 Betatesters wanted
    I WANT YOU - outlook for ETH + POE + USB high speed version
2025-09-02 Fix wrong date
2025-09-29 Added link to Elecrow
    And added linux gpib firmware binary.
    The linux gpib firmware sourcecode is about to get added soon together with a explanatory documented.
2025-10-20 Adding a first Tutorial
    Linux R&S Visa + Python with Pyvisa tutorial.
    Also restructured the main readme.md a bit.
2025-10-20 Add some more links / update documentatio
2025-10-21 fix a link + add idention
2025-10-29 Added a tutorial for windows
2025-11-23 Adding new USer manual
    See tutorials section to access it.
2025-11-30 Updaste to firmware Version V2.2
    All 256 termination characters are now possible.
    And 2 further bugfixes.
    -> See 30th November update in updates.md for more details.
2025-12-24 V3 sneak preview and status added
2025-12-24 Update V3 Sneak preview picture
    such that it renders better
2025-12-24 update image link to v3 sneak preview
    sorry for pushing that often, handling pictures in .MDs is a bit painful on Github.
2025-12-30 Added link to Digikey US
2026-02-01 Add new MArkdown version of the manual and extend the Manual with a FAQ
2026-02-04 Add Markdown version of the documentation, Update Firmware to version V2.3
    - The PDF versions are still there. Both PDF and Markdown are autogenerated from a single source document for consistency.
    Markdown enables easier linking to information for support, etc. compared the PDF. PDF has the advantage of better readability.
    Furthermore Firmware version got upgraded to V2.3.
    Changes:
    - when using autoid, characters which are not allowed as USBTMC serial number got replaced by underscores. This could end up in situation where 2 underscores follow each other. Keysight Visa crashes 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
    - Addressed Issues #9
2026-02-04 updated table of contents in PDF Manual
    The FAQ entry was not showing up in TOC.
2026-02-04 Adding a statement on HW clones sold online
    shocked.
2026-02-04 refined statement on clones
2026-03-07 Updates
    Elecrow has stock again!
    GPIBee = UsbGpib V3 actual photo and update
2026-04-18 Added Command to set GPIB address
    A newly added command is added (!addr primary [secondary] to allow communication with multiple GPIB instruments.
    Documentation is updated in next push.
2026-04-18 Added notes on the new V2.4 firmware implementation and GPIBee
2026-04-18 Delete BOMV2.html
    to avoid inconsistences! Use BOM-xyp-gpib.csv as source of truth!
2026-05-02 Add a comment on how to update the firmware using Linux

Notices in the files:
parts and their libraries:
Copyright 2016 Accelerated Designs. All rights reserved.
